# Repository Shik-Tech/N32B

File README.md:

# N32B - Midi Controller
N32B Midi controller is an open source hardware and software.
We use the arduino pro micro as the heart of the controller. The N32B is basically an arduino shield and easy to solder project.

You can contribute, build your own or buy a full working device.

You will find the schematics and board layout files in this repository.
Feel free to fork, we would love to see what you created!

# Firmware Repositories
A separate repositories are available for the device firmware variations:

Midi CC firmware:
https://github.com/Shik-Tech/N32B_HiRes

SysEx firmware:
https://github.com/Shik-Tech/N32B-sysEx

## Licensing

Hardware and documentation license is under CC0 1.0 Universal.

Firemware license is under MIT License.

You can find more details about licensing here: https://github.com/Shik-Tech/N32B/blob/master/LICENSE.md

## Additional Information
For more information please visit https://shik.tech

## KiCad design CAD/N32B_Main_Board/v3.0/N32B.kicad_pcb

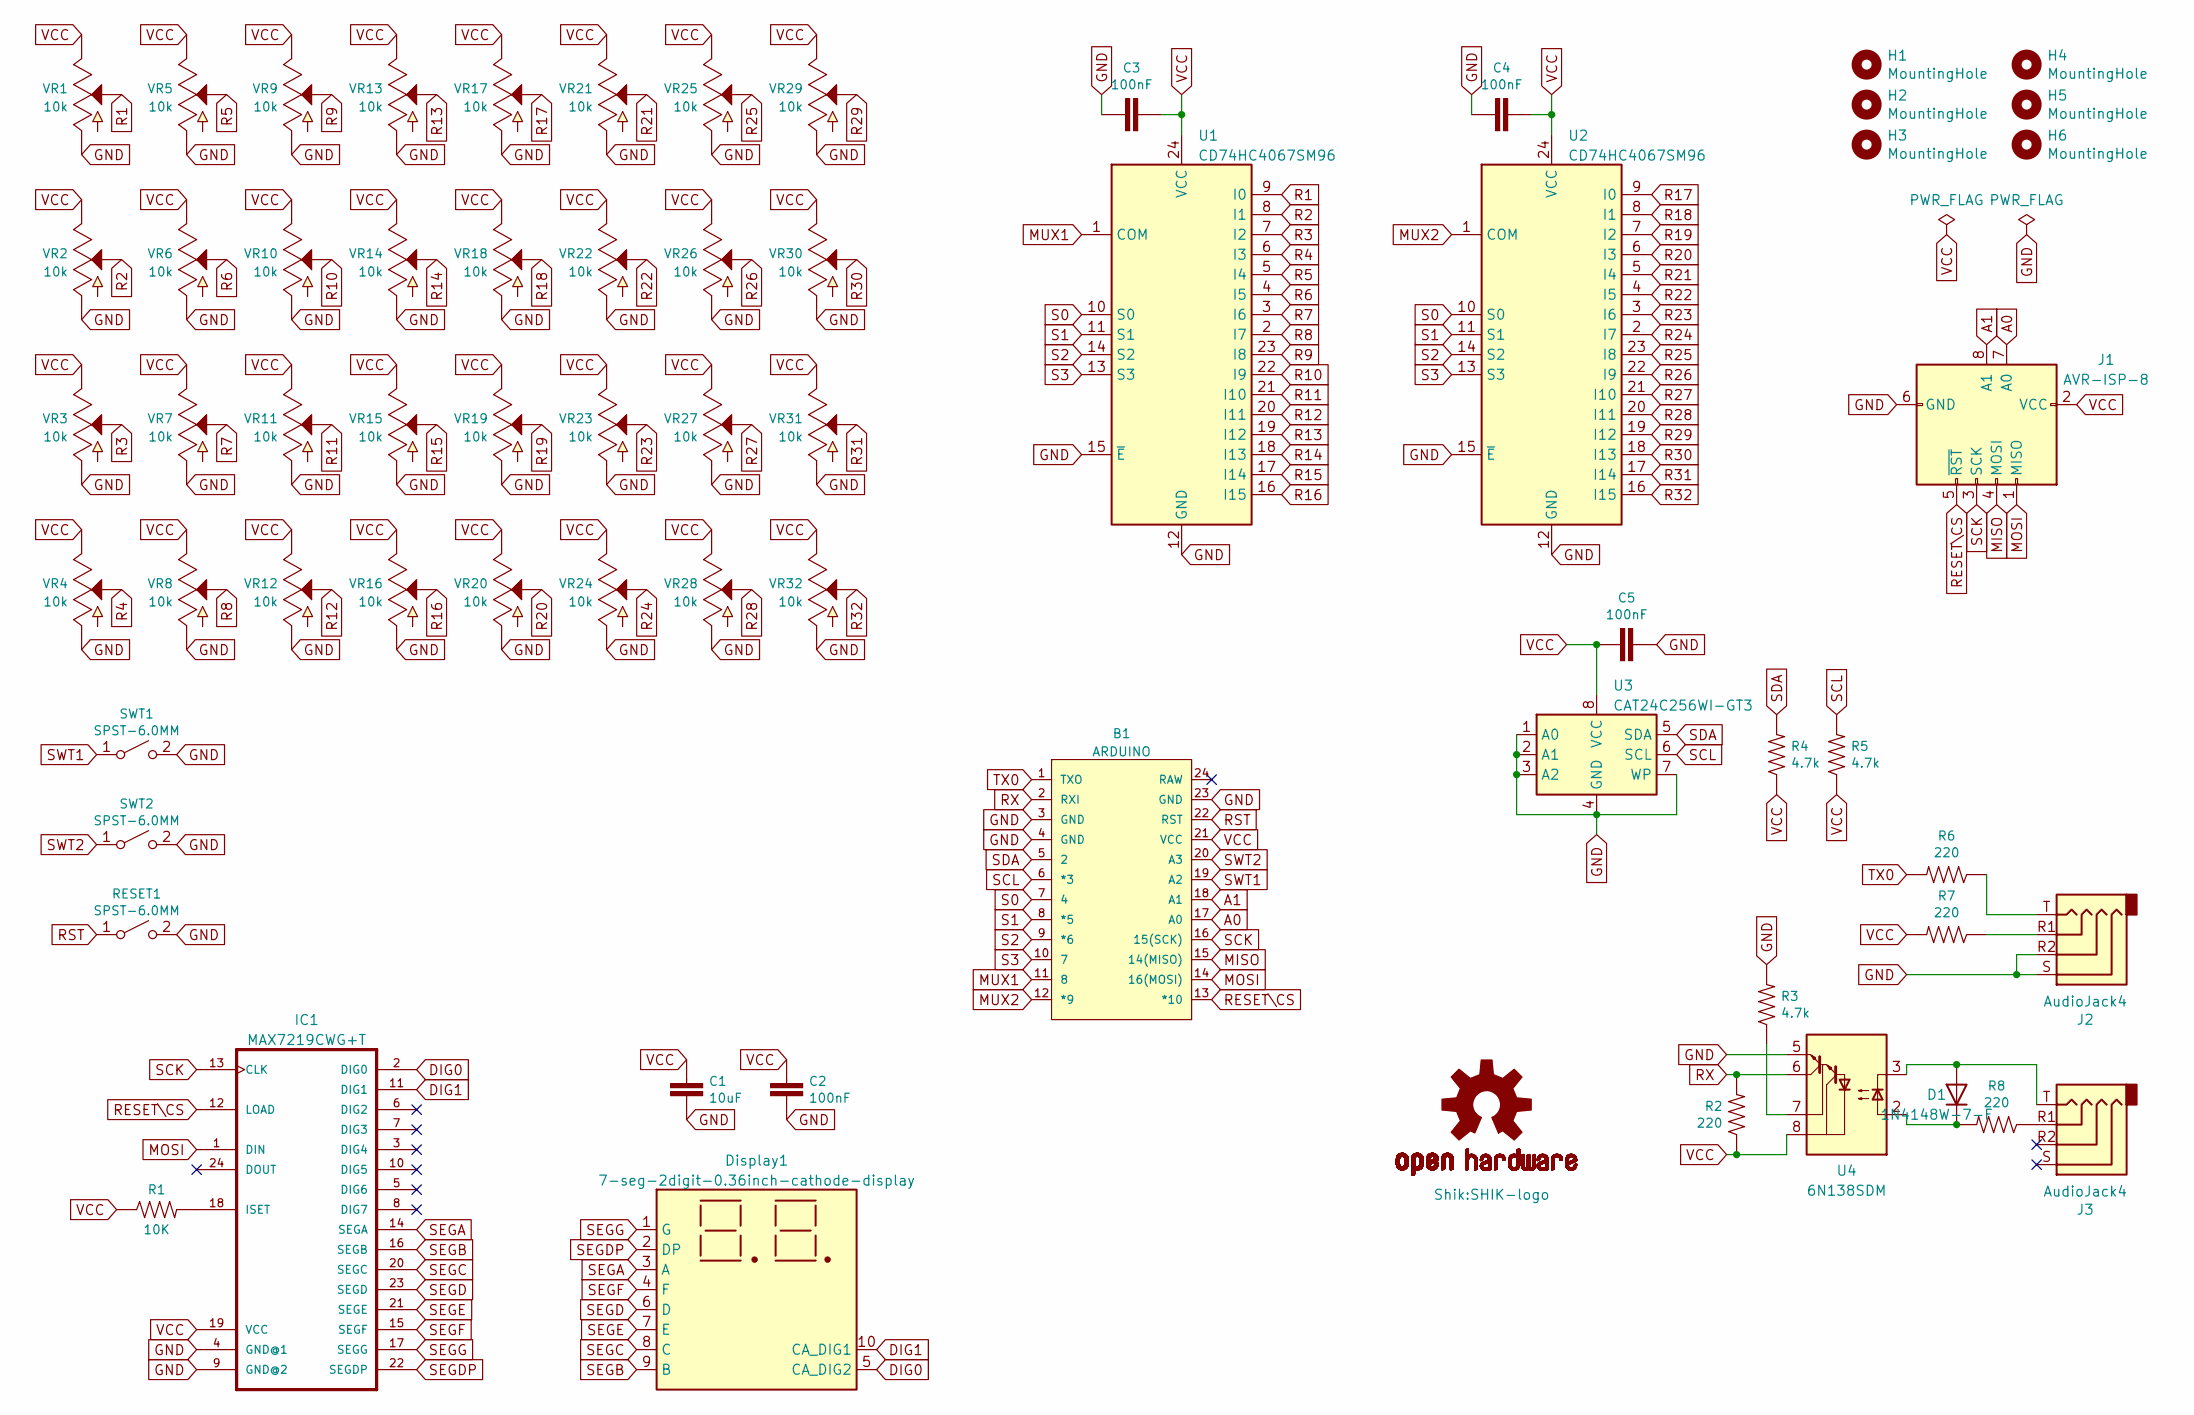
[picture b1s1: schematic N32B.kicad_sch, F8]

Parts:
B1: ARDUINO; ARDUINO_PRO_MICRO
C1: 10uF; 0603
C2, C3, C4, C5: 100nF; 0603
D1: 1N4148W-7-F; SOD-123
Display1: 7-seg-2digit-0.36inch-cathode-display; 7-Segment-2-Digits-0.36inch
H1, H2, H3, H4, H5, H6: MountingHole; MountingHole_3.2mm_M3
IC1: MAX7219CWG+T; SOIC-24_W7.50mm
J1: AVR-ISP-8; Connector-2x04-pin
J2, J3: AudioJack4; Jack_3.5mm_Horizontal
LOGO1: OSHW-LOGOS; OSHW-LOGO-S
LOGO2: SHIK-Logo; SHIK-logo
R1: 10K; 0603
R2, R6, R7, R8: 220; 0603
R3, R4, R5: 4.7k; 0603
RESET1: SPST-6.0MM; TACTILE_SWITCH_PTH_6.0MM
SWT1, SWT2: SPST-6.0MM; TACTILE_SWITCH_PTH_6.0MM
U1, U2: CD74HC4067SM96; SSOP24
U3: CAT24C256WI-GT3; SOIC-8_W3.9mm
U4: 6N138SDM; 6n138SDM
VR1, VR2, VR3, VR4, VR5, VR6, VR7, VR8, VR9, VR10, VR11, VR12, VR13, VR14, VR15, VR16, VR17, VR18, VR19, VR20, VR21, VR22, VR23, VR24, VR25, VR26, VR27, VR28, VR29, VR30, VR31, VR32: 10k; POT-PTH-ALPS-KIT

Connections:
A0: B1.17 (A0), J1.7 (A0)
A1: B1.18 (A1), J1.8 (A1)
DIG0: Display1.5 (CA_DIG2), IC1.2 (DIG0)
DIG1: Display1.10 (CA_DIG1), IC1.11 (DIG1)
GND: B1.3 (GND), B1.4 (GND), B1.23 (GND), C1.2, C2.2, C3.1, C4.1, C5.1, IC1.4 (GND@1), IC1.9 (GND@2), J1.6 (GND), J2.R2, J2.S, R3.2, RESET1.2 (B), SWT1.2 (B), SWT2.2 (B), U1.12 (GND), U1.15 (~E), U2.12 (GND), U2.15 (~E), U3.1 (A0), U3.2 (A1), U3.3 (A2), U3.4 (GND), U3.7 (WP), U4.5 (GND), VR1.P$3 (A), VR2.P$3 (A), VR3.P$3 (A), VR4.P$3 (A), VR5.P$3 (A), VR6.P$3 (A), VR7.P$3 (A), VR8.P$3 (A), VR9.P$3 (A), VR10.P$3 (A), VR11.P$3 (A), VR12.P$3 (A), VR13.P$3 (A), VR14.P$3 (A), VR15.P$3 (A), VR16.P$3 (A), VR17.P$3 (A), VR18.P$3 (A), VR19.P$3 (A), VR20.P$3 (A), VR21.P$3 (A), VR22.P$3 (A), VR23.P$3 (A), VR24.P$3 (A), VR25.P$3 (A), VR26.P$3 (A), VR27.P$3 (A), VR28.P$3 (A), VR29.P$3 (A), VR30.P$3 (A), VR31.P$3 (A), VR32.P$3 (A)
MISO: B1.15 (14(MISO)), J1.4 (MOSI)
MOSI: B1.14 (16(MOSI)), IC1.1 (DIN), J1.1 (MISO)
MUX1: B1.11 (8), U1.1 (COM)
MUX2: B1.12 (*9), U2.1 (COM)
unnamed: D1.1 (K), R8.2, U4.2 (C1)
unnamed: D1.2 (A), J3.T, U4.3 (C2)
unnamed: IC1.18 (ISET), R1.2
unnamed: J2.R1, R7.1
unnamed: J2.T, R6.1
unnamed: J3.R1, R8.1
unnamed: R3.1, U4.7 (VO1)
R1: U1.9 (I0), VR1.P$2 (S)
R2: U1.8 (I1), VR2.P$2 (S)
R3: U1.7 (I2), VR3.P$2 (S)
R4: U1.6 (I3), VR4.P$2 (S)
R5: U1.5 (I4), VR5.P$2 (S)
R6: U1.4 (I5), VR6.P$2 (S)
R7: U1.3 (I6), VR7.P$2 (S)
R8: U1.2 (I7), VR8.P$2 (S)
R9: U1.23 (I8), VR9.P$2 (S)
R10: U1.22 (I9), VR10.P$2 (S)
R11: U1.21 (I10), VR11.P$2 (S)
R12: U1.20 (I11), VR12.P$2 (S)
R13: U1.19 (I12), VR13.P$2 (S)
R14: U1.18 (I13), VR14.P$2 (S)
R15: U1.17 (I14), VR15.P$2 (S)
R16: U1.16 (I15), VR16.P$2 (S)
R17: U2.9 (I0), VR17.P$2 (S)
R18: U2.8 (I1), VR18.P$2 (S)
R19: U2.7 (I2), VR19.P$2 (S)
R20: U2.6 (I3), VR20.P$2 (S)
R21: U2.5 (I4), VR21.P$2 (S)
R22: U2.4 (I5), VR22.P$2 (S)
R23: U2.3 (I6), VR23.P$2 (S)
R24: U2.2 (I7), VR24.P$2 (S)
R25: U2.23 (I8), VR25.P$2 (S)
R26: U2.22 (I9), VR26.P$2 (S)
R27: U2.21 (I10), VR27.P$2 (S)
R28: U2.20 (I11), VR28.P$2 (S)
R29: U2.19 (I12), VR29.P$2 (S)
R30: U2.18 (I13), VR30.P$2 (S)
R31: U2.17 (I14), VR31.P$2 (S)
R32: U2.16 (I15), VR32.P$2 (S)
RESET\CS: B1.13 (*10), IC1.12 (LOAD), J1.5 (~RST)
RST: B1.22 (RST), RESET1.1 (A)
RX: B1.2 (RXI), R2.2, U4.6 (VO2)
S0: B1.7 (4), U1.10 (S0), U2.10 (S0)
S1: B1.8 (*5), U1.11 (S1), U2.11 (S1)
S2: B1.9 (*6), U1.14 (S2), U2.14 (S2)
S3: B1.10 (7), U1.13 (S3), U2.13 (S3)
SCK: B1.16 (15(SCK)), IC1.13 (CLK), J1.3 (SCK)
SCL: B1.6 (*3), R5.2, U3.6 (SCL)
SDA: B1.5 (2), R4.2, U3.5 (SDA)
SEGA: Display1.3 (A), IC1.14 (SEGA)
SEGB: Display1.9 (B), IC1.16 (SEGB)
SEGC: Display1.8 (C), IC1.20 (SEGC)
SEGD: Display1.6 (D), IC1.23 (SEGD)
SEGDP: Display1.2 (DP), IC1.22 (SEGDP)
SEGE: Display1.7 (E), IC1.21 (SEGE)
SEGF: Display1.4 (F), IC1.15 (SEGF)
SEGG: Display1.1 (G), IC1.17 (SEGG)
SWT1: B1.19 (A2), SWT1.1 (A)
SWT2: B1.20 (A3), SWT2.1 (A)
TX0: B1.1 (TXO), R6.2
VCC: B1.21 (VCC), C1.1, C2.1, C3.2, C4.2, C5.2, IC1.19 (VCC), J1.2 (VCC), R1.1, R2.1, R4.1, R5.1, R7.2, U1.24 (VCC), U2.24 (VCC), U3.8 (VCC), U4.8 (VCC), VR1.P$1 (E), VR2.P$1 (E), VR3.P$1 (E), VR4.P$1 (E), VR5.P$1 (E), VR6.P$1 (E), VR7.P$1 (E), VR8.P$1 (E), VR9.P$1 (E), VR10.P$1 (E), VR11.P$1 (E), VR12.P$1 (E), VR13.P$1 (E), VR14.P$1 (E), VR15.P$1 (E), VR16.P$1 (E), VR17.P$1 (E), VR18.P$1 (E), VR19.P$1 (E), VR20.P$1 (E), VR21.P$1 (E), VR22.P$1 (E), VR23.P$1 (E), VR24.P$1 (E), VR25.P$1 (E), VR26.P$1 (E), VR27.P$1 (E), VR28.P$1 (E), VR29.P$1 (E), VR30.P$1 (E), VR31.P$1 (E), VR32.P$1 (E)

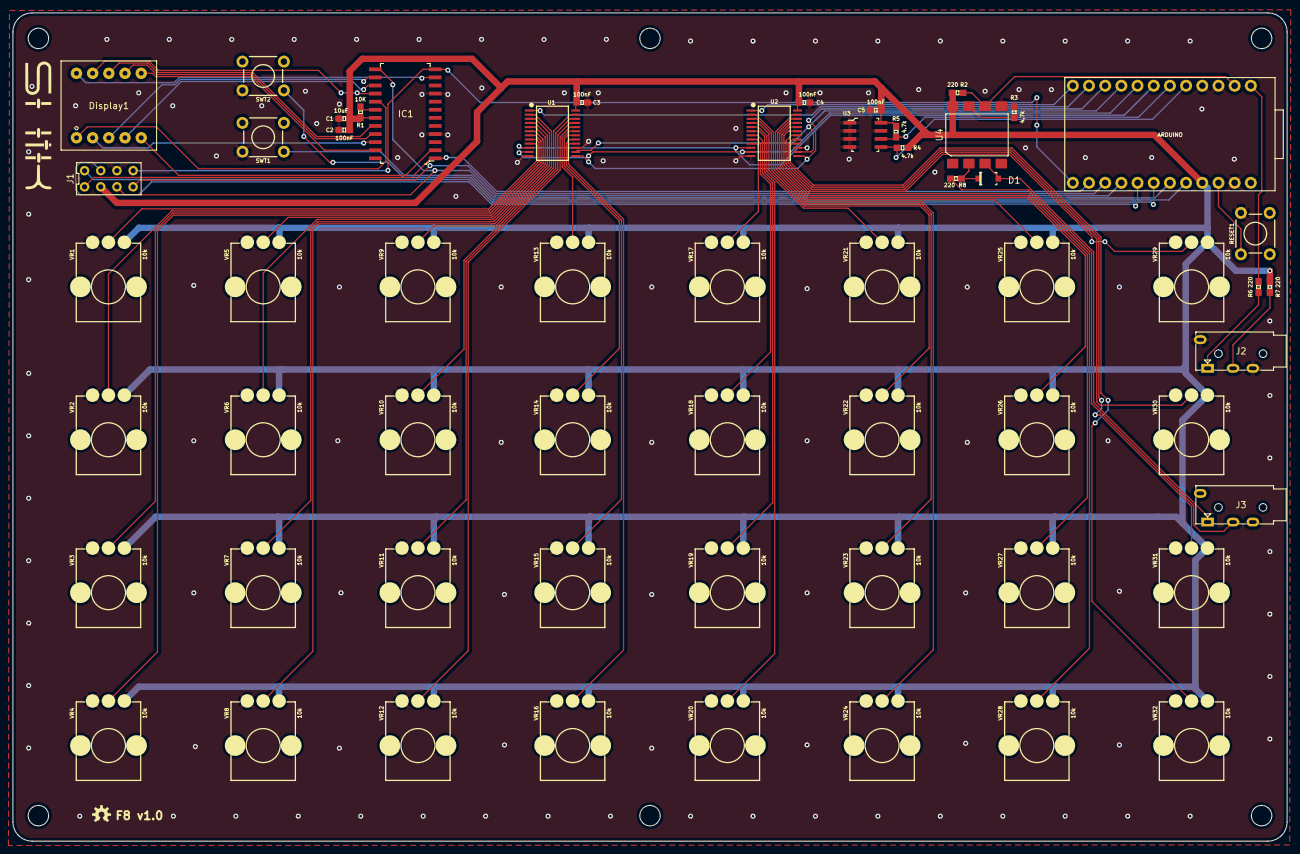
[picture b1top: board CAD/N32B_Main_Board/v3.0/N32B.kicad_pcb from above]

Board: 2 copper layers, 200.0 x 130.0 mm, 67 parts (0 on the bottom side), 70 nets.

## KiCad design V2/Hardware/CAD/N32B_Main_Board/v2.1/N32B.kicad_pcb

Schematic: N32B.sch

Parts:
B1: ARDUINO_PRO_MICRO_5V; ARDUINO_PRO_MICRO
C1: 100nF; CAP-PTH-5.08
C2: 10uF; CAP-PTH-5.08
D1: 1N914; D_DO-35_SOD27_P7.62mm_Horizontal
DEV1: GND VCC CS MOSI MISO CLK A0 A1 D6 D7; PinHeader_2x05_P2.54mm_Vertical
Display1: 7-segment-2digit-0.36inch-display; 7-Segment-2-Digits-0.36inch
H1, H2, H3, H4, H5, H6: MountingHole; MountingHole_3.2mm_M3
IC1: MAX7219CNG; DIL24-3
J1, J2: AudioJack4; Jack_3.5mm_Horizontal
MUX1, MUX2: 16-CHANNEL-ANALOG-MULTIPLEXER; XDCR_BOB-09056
R1, R2, R3, R5: 220; AXIAL-0.3-KIT
R4: 4.7k; AXIAL-0.3-KIT
R10: 10K; AXIAL-0.3-KIT
RESET1: MOMENTARY-SWITCH-SPST-PTH-6.0MM; TACTILE_SWITCH_PTH_6.0MM
SWT1, SWT2: MOMENTARY-SWITCH-SPST-PTH-6.0MM; TACTILE_SWITCH_PTH_6.0MM
U1: 6N138; 6n138
VR1, VR2, VR3, VR4, VR5, VR6, VR7, VR8, VR9, VR10, VR11, VR12, VR13, VR14, VR15, VR16, VR17, VR18, VR19, VR20, VR21, VR22, VR23, VR24, VR25, VR26, VR27, VR28, VR29, VR30, VR31, VR32: 10k; Potentiometer_R09_B103_Single_Vertical

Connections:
/Analog0: B1.17, DEV1.7
/Analog1: B1.18, DEV1.8
/Digital6: B1.9, DEV1.10
/Digital7: B1.10, DEV1.9
CLK: B1.16, DEV1.6, IC1.13
CS: B1.13, DEV1.4, IC1.12
DIG0: Display1.5, IC1.2
DIG1: Display1.10, IC1.11
GND: B1.3, B1.4, B1.23, C1.2, C2.2, DEV1.1, IC1.4, IC1.9, J1.R2, J1.S, MUX1.1, MUX1.3, MUX2.1, MUX2.3, R4.P$2, RESET1.3, SWT1.3, SWT2.3, U1.5, VR1.1, VR2.1, VR3.1, VR4.1, VR5.1, VR6.1, VR7.1, VR8.1, VR9.1, VR10.1, VR11.1, VR12.1, VR13.1, VR14.1, VR15.1, VR16.1, VR17.1, VR18.1, VR19.1, VR20.1, VR21.1, VR22.1, VR23.1, VR24.1, VR25.1, VR26.1, VR27.1, VR28.1, VR29.1, VR30.1, VR31.1, VR32.1
MISO: B1.15, DEV1.5
MOSI: B1.14, DEV1.3, IC1.1
MUX1: B1.11, MUX1.8
MUX2: B1.12, MUX2.8
unnamed: D1.1, R3.P$2, U1.2
unnamed: D1.2, J2.T, U1.3
unnamed: IC1.18, R10.P$2
unnamed: J1.R1, R1.P$1
unnamed: J1.T, R2.P$1
unnamed: J2.R1, R3.P$1
unnamed: R4.P$1, U1.7
R1: MUX1.9, VR1.2
R2: MUX1.10, VR2.2
R3: MUX1.12, VR3.2
R4: MUX1.15, VR4.2
R5: MUX2.9, VR5.2
R6: MUX2.16, VR6.2
R7: MUX2.20, VR7.2
R8: MUX2.24, VR8.2
R9: MUX1.11, VR9.2
R10: MUX1.13, VR10.2
R11: MUX1.14, VR11.2
R12: MUX1.22, VR12.2
R13: MUX2.10, VR13.2
R14: MUX2.15, VR14.2
R15: MUX2.19, VR15.2
R16: MUX2.23, VR16.2
R17: MUX1.16, VR17.2
R18: MUX1.17, VR18.2
R19: MUX1.20, VR19.2
R20: MUX1.23, VR20.2
R21: MUX2.11, VR21.2
R22: MUX2.14, VR22.2
R23: MUX2.18, VR23.2
R24: MUX2.22, VR24.2
R25: MUX1.18, VR25.2
R26: MUX1.19, VR26.2
R27: MUX1.21, VR27.2
R28: MUX1.24, VR28.2
R29: MUX2.12, VR29.2
R30: MUX2.13, VR30.2
R31: MUX2.17, VR31.2
R32: MUX2.21, VR32.2
RST: B1.22, RESET1.1
RX: B1.2, R5.P$2, U1.6
S0: B1.5, MUX1.4, MUX2.4
S1: B1.6, MUX1.5, MUX2.5
S2: B1.7, MUX1.6, MUX2.6
S3: B1.8, MUX1.7, MUX2.7
SEGA: Display1.3, IC1.14
SEGB: Display1.9, IC1.16
SEGC: Display1.8, IC1.20
SEGD: Display1.6, IC1.23
SEGDP: Display1.2, IC1.22
SEGE: Display1.7, IC1.21
SEGF: Display1.4, IC1.15
SEGG: Display1.1, IC1.17
SWT1: B1.19, SWT1.1
SWT2: B1.20, SWT2.1
TX0: B1.1, R2.P$2
VCC: B1.21, C1.1, C2.1, DEV1.2, IC1.19, MUX1.2, MUX2.2, R1.P$2, R5.P$1, R10.P$1, U1.8, VR1.3, VR2.3, VR3.3, VR4.3, VR5.3, VR6.3, VR7.3, VR8.3, VR9.3, VR10.3, VR11.3, VR12.3, VR13.3, VR14.3, VR15.3, VR16.3, VR17.3, VR18.3, VR19.3, VR20.3, VR21.3, VR22.3, VR23.3, VR24.3, VR25.3, VR26.3, VR27.3, VR28.3, VR29.3, VR30.3, VR31.3, VR32.3

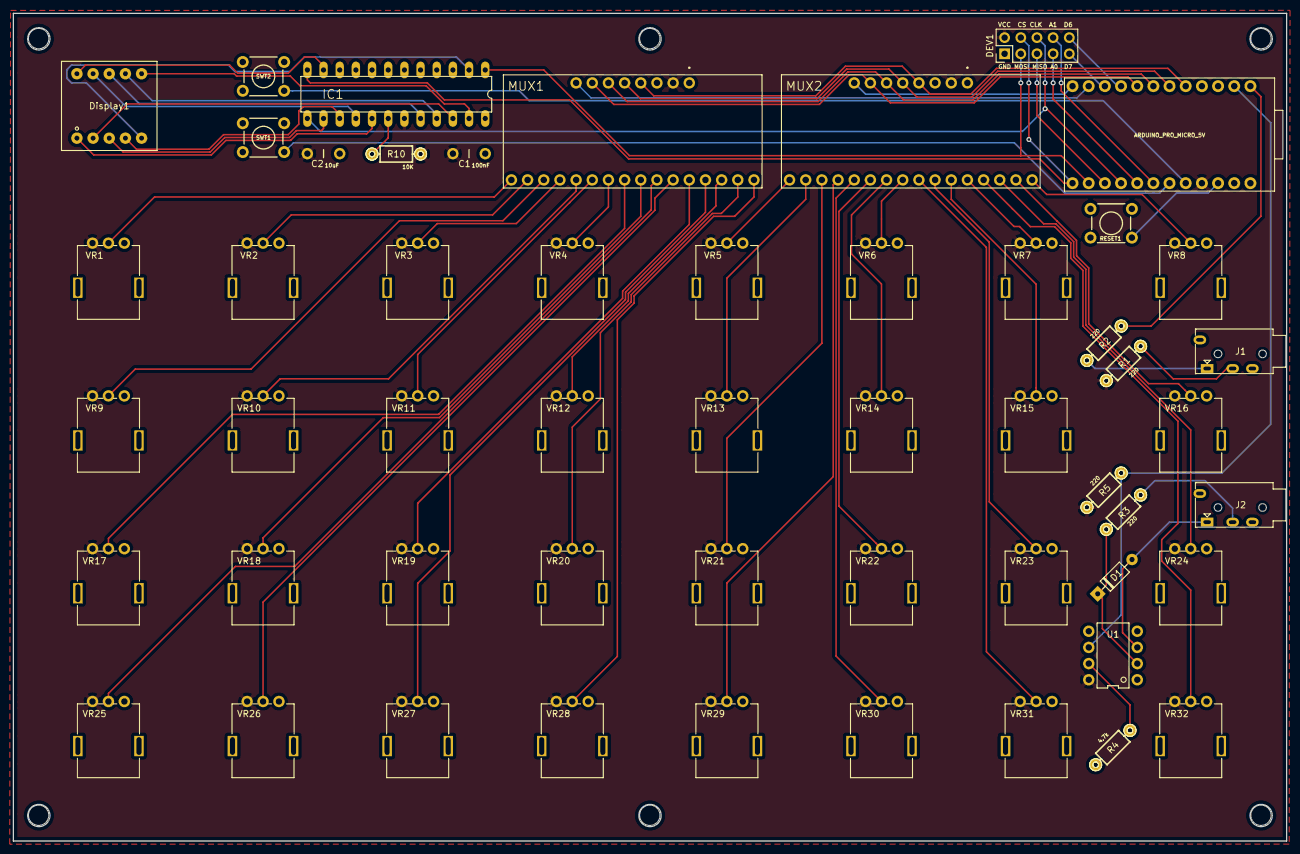
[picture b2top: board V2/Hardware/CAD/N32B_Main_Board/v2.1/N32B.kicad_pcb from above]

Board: 2 copper layers, 200.0 x 130.0 mm, 59 parts (0 on the bottom side), 70 nets.

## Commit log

2020-08-23 Create LICENSE
2020-08-23 Rename LICENSE to LICENSE.md
2020-08-23 Added top panel stl file
2020-08-23 Added Board plots
2020-09-06 Initial update
2020-09-06 Update schematics
2020-09-09 Adding kicad sources
2020-09-10 Added display & midi CC. Both midiUsb and MIdiDin
2020-09-16 Hardware upgrades
2020-09-16 Display as class
2021-02-04 Version 2.0
2021-02-04 Plot directory
2021-02-09 Dynamic memory improvment
2021-02-10 Display - midi I/O indicator. Reduced active leds.
2021-02-10 Handle buttons fixes
2021-02-10 Inhibit msgs when changing channel. Display update
2021-02-10 Cleanup. Startup animation. Version
2021-02-11 Fix for NRPN. Cleanup
2021-04-01 version 2.1 - min/max value support
2021-04-01 Clean up
2021-04-01 gitignore update
2021-04-01 Feature/v2.1 (#4)
    * Dynamic memory improvment
    * Display - midi I/O indicator. Reduced active leds.
    * Handle buttons fixes
    * Inhibit msgs when changing channel. Display update
    * Cleanup. Startup animation. Version
    * Fix for NRPN. Cleanup
2021-04-01 Removed min/max CC. Moving average high precision
2021-04-18 Version update. Remove Min/Max indexes. Cleanup
2021-04-18 Better handling low res 7-bit mode
2021-04-18 Feature/v3.0 (#5)
    * Removed min/max CC. Moving average high precision
    * Version update. Remove Min/Max indexes. Cleanup
    * Better handling low res 7-bit mode
2021-04-27 License (#6)
    * Create License.svg
    * Update README.md
    * Update LICENSE.md
2021-05-03 Support the new mux design in the main board
2021-06-06 Update the enclosure files
2021-06-06 Cleanup
2021-06-06 Update the top panel stl
2021-07-10 Fixed MIDI IN issue. Added compiled hex file for v3.0.1
2021-07-11 Fix for Midi IN
2021-10-25 Hardware updates v2.2
2022-06-26 Update README.md
    Firmware notice
2022-09-26 Re-organize hardware versions
2023-02-22 Adding enclosure files. Cleanup.
2023-02-22 Sort enclosure files
2023-02-25 Enclosure top panels
